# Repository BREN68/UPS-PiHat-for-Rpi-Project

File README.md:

# UPS-PiHat-for-Rpi-Project
The UPS piHat provides protective circuitry as well as backup for the raspberry pi. This is meant to provide protection against power spikes in the primary input power, and also allow for safe shutdown without loss of data.

The rpi w board recomended for the project.

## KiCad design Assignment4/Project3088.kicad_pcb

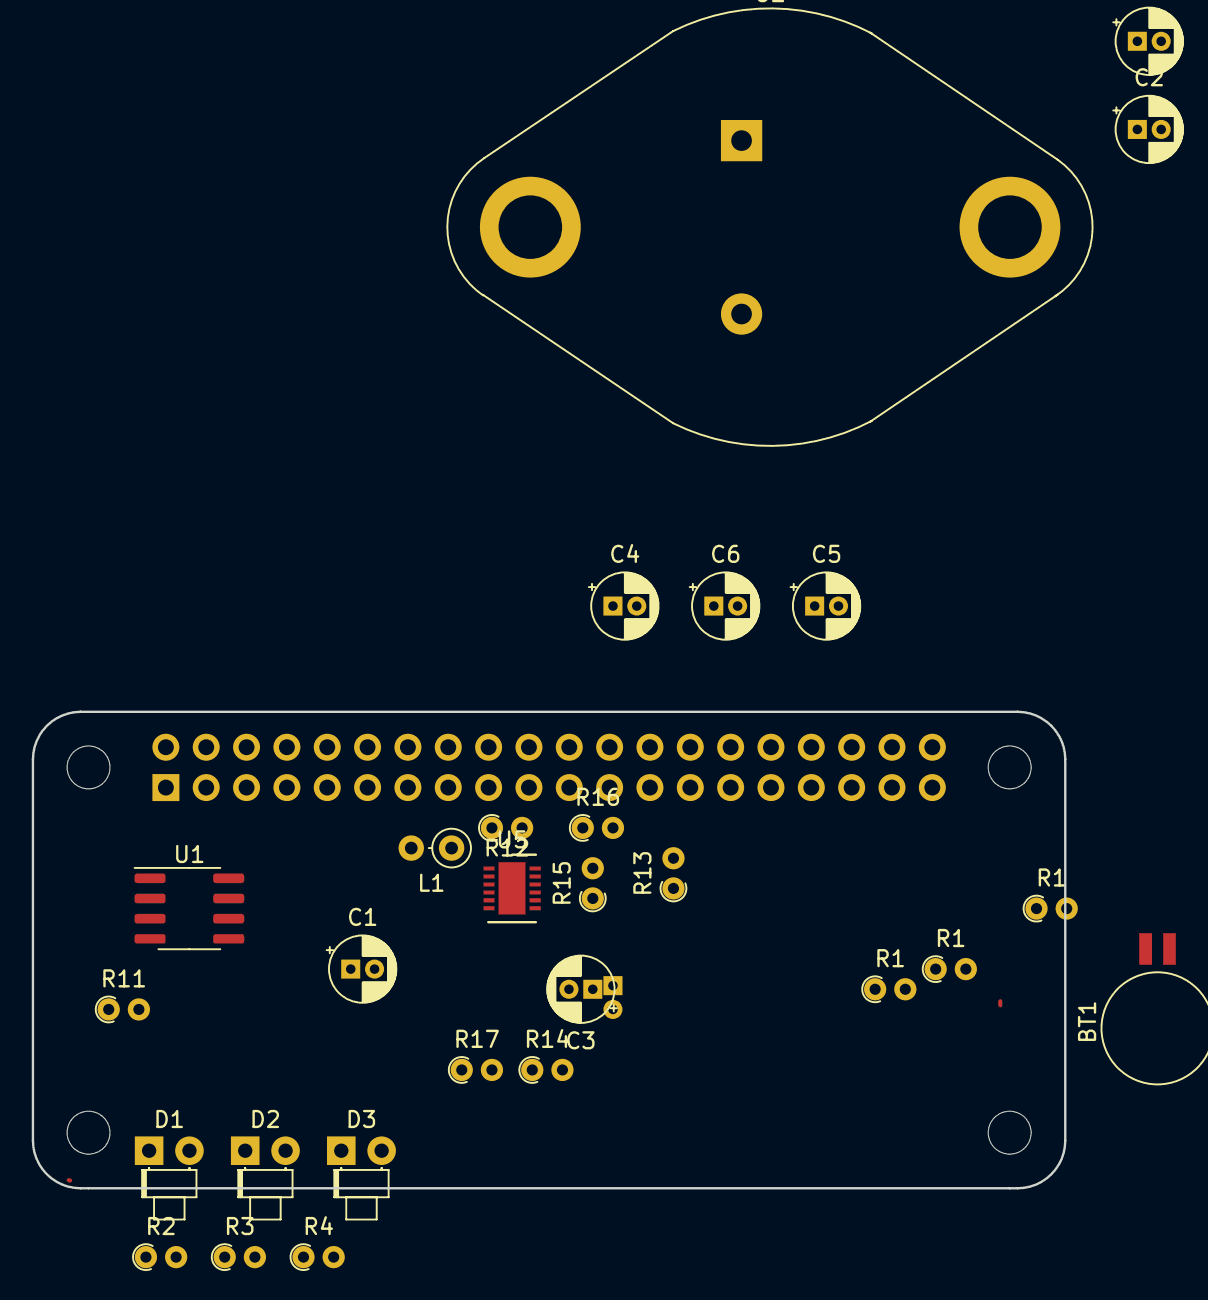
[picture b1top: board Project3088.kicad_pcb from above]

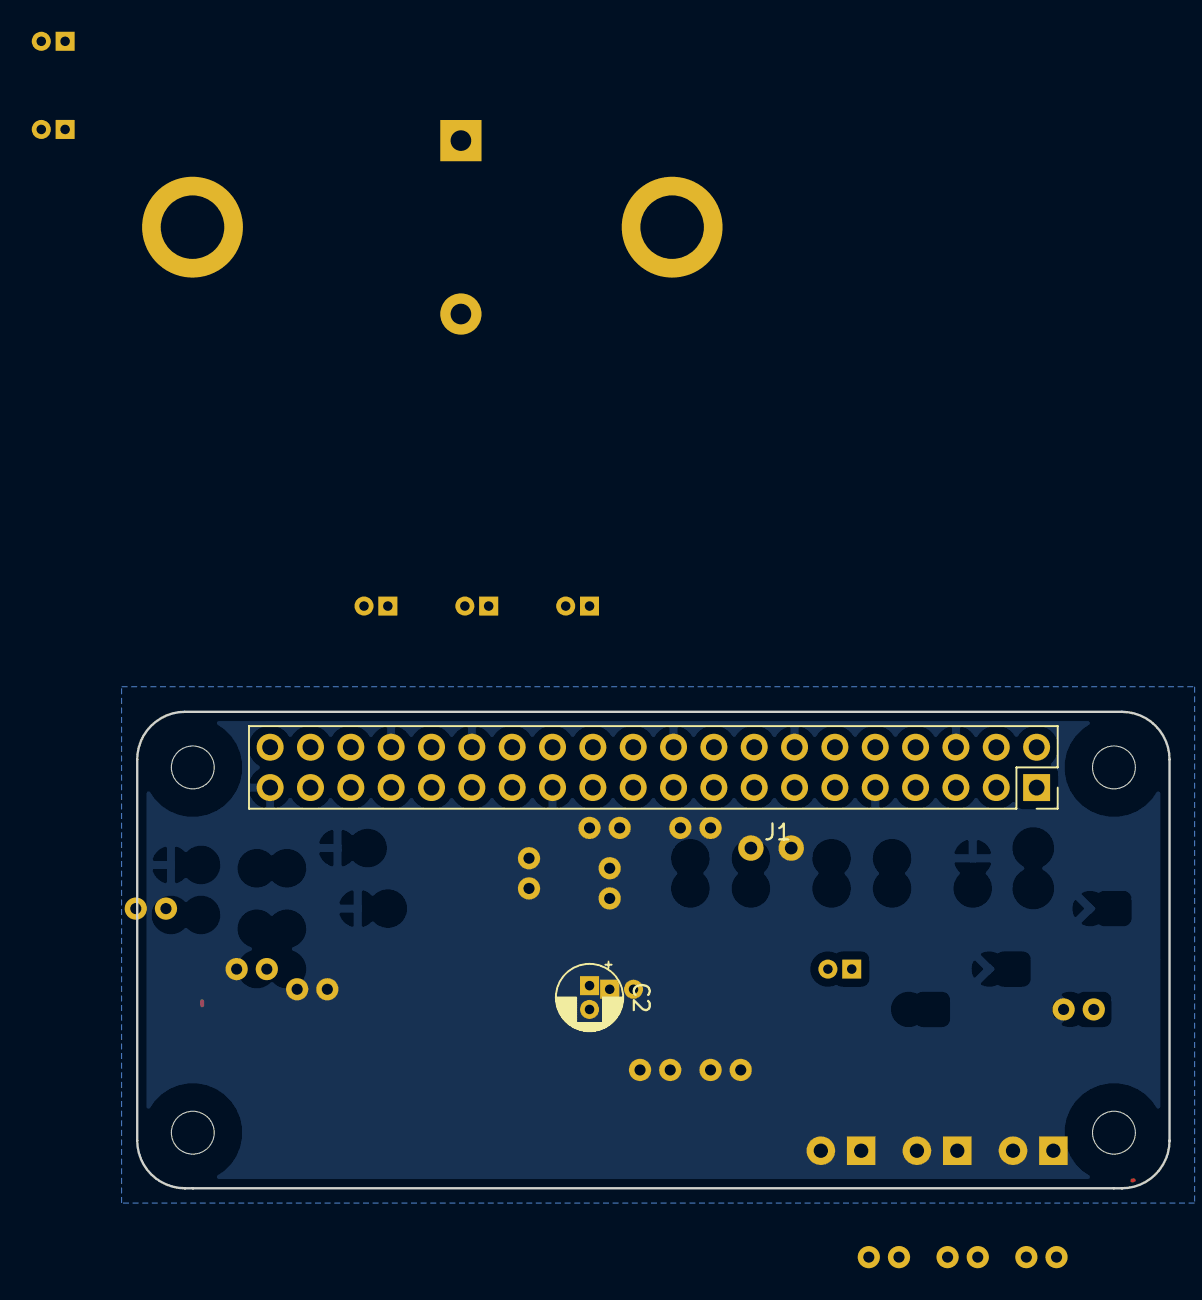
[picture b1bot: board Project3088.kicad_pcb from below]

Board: 2 copper layers, 65.0 x 30.0 mm, 34 parts (2 on the bottom side), 20 nets.

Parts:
BT1: 6V; BatteryHolder_Seiko_MS621F
C1, C1#2: 10u; CP_Radial_D4.0mm_P1.50mm
C2: 1u; CP_Radial_D4.0mm_P1.50mm
C2#2, C4: 0.01u; CP_Radial_D4.0mm_P1.50mm
C3: 560p; CP_Radial_D4.0mm_P1.50mm
C5: 150p; CP_Radial_D4.0mm_P1.50mm
C6: 47u; CP_Radial_D4.0mm_P1.50mm
D1, D2, D3: LED; LED_D1.8mm_W1.8mm_H2.4mm_Horizontal_O1.27mm_Z1.6mm
H1, H2, H3, H4: MountingHole; MountingHole_2.7mm_M2.5_uHAT_RPi
J1: GPIO_CONNECTOR; PinSocket_2x20_P2.54mm_Vertical_Centered_Anchor
L1: 5u; L_Axial_L5.3mm_D2.2mm_P2.54mm_Vertical_Vishay_IM-1
R1, R1#2, R1#3: 1K; R_Axial_DIN0204_L3.6mm_D1.6mm_P1.90mm_Vertical
R2, R3, R4: 1k; R_Axial_DIN0204_L3.6mm_D1.6mm_P1.90mm_Vertical
R11: 1M; R_Axial_DIN0204_L3.6mm_D1.6mm_P1.90mm_Vertical
R12, R13: 64.9k; R_Axial_DIN0204_L3.6mm_D1.6mm_P1.90mm_Vertical
R14: 10k; R_Axial_DIN0204_L3.6mm_D1.6mm_P1.90mm_Vertical
R15: 340k; R_Axial_DIN0204_L3.6mm_D1.6mm_P1.90mm_Vertical
R16: 200k; R_Axial_DIN0204_L3.6mm_D1.6mm_P1.90mm_Vertical
R17: 2.2k; R_Axial_DIN0204_L3.6mm_D1.6mm_P1.90mm_Vertical
U1: LM2931-5.0_SO8; SOIC-8_3.9x4.9mm_P1.27mm
U2: L7805; TO-3
U5: LTC3442; DFN-12-1EP_3x4mm_P0.5mm_EP1.7x3.3mm

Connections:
+3V3: J1.1, J1.17
+BATT: C1.2, C1#2.1, D1.2, R11.1, U2.1, U5.9
/powerSupply/Out: C6.1, R15.1, R17.1, U5.8
GND: BT1.2, C1.1, C1#2.2, C2.2, C2#2.2, C4.2, C6.2, J1.6, J1.9, J1.14, J1.20, J1.25, J1.30, J1.34, J1.39, R2.2, R3.2, R4.2, R12.2, R13.2, R16.2, U1.2, U1.3, U1.6, U1.7, U2.2, U5.3, U5.5, U5.10
unnamed: BT1.1, R1.2, R1#2.2, R1#3.2
unnamed: C2#2.1, R11.2, U5.1
unnamed: C3.1, C5.2, R15.2, R16.1, U5.12
unnamed: C3.2, R14.1
unnamed: C4.1, R13.1, U5.7
unnamed: C5.1, R17.2
unnamed: D1.1, D2.2, R2.1
unnamed: D2.1, D3.2, R3.1
unnamed: D3.1, R4.1
unnamed: J1.2, U1.1
unnamed: L1.1, U5.4
unnamed: L1.2, U5.6
unnamed: R1.1, R1#2.1, R1#3.1, U1.8
unnamed: R12.1, U5.2
unnamed: R14.2, U5.11
Vo: C2.1, U2.3

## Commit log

2021-05-13 Update README.md
    The rpi board recommended for the piHat
2021-05-13 Create Prologue
    Beginning of the need of the project
2021-06-04 Create Subsystems
2021-06-05 Create Power Subsystem
2021-06-05 Create StatusLED subsystem
2021-06-05 Create Amplifier Subsystem
2021-06-06 Update StatusLED subsystem
    Status leds functionality
2021-06-06 Create Amp
2021-06-06 Add files via upload
    sources
2021-06-06 Create ERC
2021-06-06 Add files via upload
    option
2021-06-11 Create erc.txt
    Files from assignment 4
2021-06-11 Add files via upload
    Assignment 4 upload

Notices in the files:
Assignment4/Project3088.kicad_pcb:
This PCB design is licensed under MIT Open Source License.
